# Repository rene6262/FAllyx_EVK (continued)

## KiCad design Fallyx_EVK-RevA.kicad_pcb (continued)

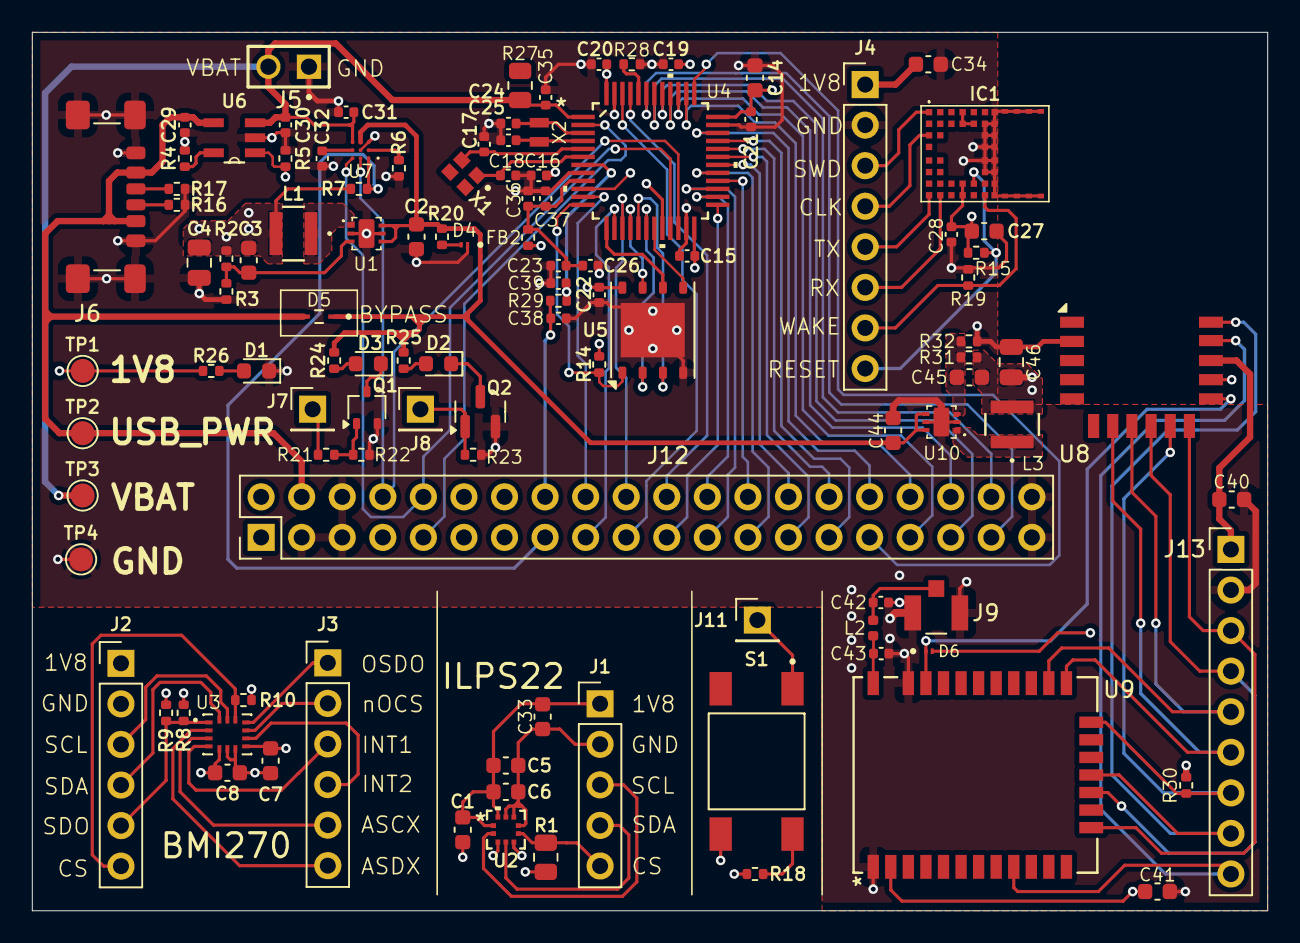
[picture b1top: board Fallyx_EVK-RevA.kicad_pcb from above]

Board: 4 copper layers, 77.3 x 55.0 mm, 112 parts (0 on the bottom side), 95 nets.

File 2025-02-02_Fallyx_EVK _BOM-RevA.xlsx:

Fallyx_EVK BOM |  | RevA
Estimated Cost | 35.42048
Designator | Mfg | Mfg Part ID | Description | QTY | COST/100 | Value | Footprint | ALT P/N
C1, C5, C7, C8, C15, C16, C19, C20, C21, C22, C26, C28, C36 | YAGEO | CC0603KRX7R7BB104 | CAP CER 0.1UF 16V X7R 0603 | 13.0 | 0.0174 | 0.1uF | C0603
C2, C6, C14, C27, C41 | Samsung Electro-Mechanics | CL10A475KP8NNNC | CAP CER 4.7UF 10V X5R 0603 | 5.0 | 0.0171 | 4.7uF | C0603
C3 | KEMET | C0603C151J5GACTU | CAP CER 150PF 50V C0G/NP0 0603 | 1.0 | 0.0164 | 150pF | C0603
C4 | Murata Electronics | GRM21BR61C106KE15K | CAP CER 10UF 16V X5R 0805 | 1.0 | 0.0467 | 10uF | C0805
C23, C31, C35, C37 | Taiyo Yuden | JMK105BJ105KV-F | CAP CER 1UF 6.3V X5R 0402 | 4.0 | 0.0144 | 1uF | C0402
C29, C30 | Murata Electronics | GRM155R60J106ME05D | CAP CER 10UF 6.3V X5R 0402 | 2.0 | 0.0235 | 10uF | C0402
C33 | Samsung Electro-Mechanics | CL10A225KO8NNNC | CAP CER 2.2UF 16V X5R 0603 | 1.0 | 0.0234 | 2.2uF | C0603
C38 | Murata Electronics | GCM155R71H223KA55D | CAP CER 0.022UF 50V X7R 0402 | 1.0 | 0.0128 | 22nF | C0402
C17, C18, C24, C25, C39 | Murata Electronics | GRM1555C1H100JA01D | CAP CER 10PF 50V C0G/NP0 0402 | 5.0 | 0.0116 | 10pF | C0402
C32 | Murata Electronics | GRM155R61A474KE15D | CAP CER 0.47UF 10V X5R 0402 | 1.0 | 0.0364 | 0.47uF | C0402
C34, C40 | Samsung Electro-Mechanics | CL10A226MP8NUNE | CAP CER 22UF 10V X5R 0603 | 2.0 | 0.0714 | 22uF | C0603
D1 | Würth Elektronik | 150060VS75000 | LED GREEN CLEAR 0603 SMD | 1.0 | 0.1098 |  | C0603
D2 | Würth Elektronik | 150060SS75000 | LED RED CLEAR 0603 SMD | 1.0 | 0.1098 |  | C0603
D3 | Würth Elektronik | 150060AS75000 | LED AMBER CLEAR 0603 SMD | 1.0 | 0.1098 |  | C0603
D4 | Kingbright | APG0603SURC-TT | LED RED CLEAR 2SMD | 1.0 | 0.1937 |  | C0201
D5 | onsemi | RB521S30T1G | DIODE SCHOTTKY 30V 200MA SOD523 | DNP | 0.044 |  | SOD523
FB2 | Würth Elektronik | 7427927261 | FERRITE BEAD 600 OHM 0402 4LN | 1.0 | 0.1485
J1 |  |  | 5PIN | DNP
J2, J3 |  |  | 6PIN | DNP
J4 |  |  | 8PIN | DNP
J5 |  |  | DNP | DNP
J6 | GCT | GCT_USB4135-GF-A | USB C REC GF RA 6P SMT & SMT SHE | 1.0 | 0.4418
J12 |  |  | 40PIN | DNP
J13 |  |  | 9PIN | DNP
L1 | Taiyo Yuden | NR3015T4R7M | FIXED IND 4.7UH 1.04A 144MOHM SM | 1.0 | 0.1881 | 4.7uH
R1 | Panasonic Electronic Components | ERJ-6GEY0R00V | RES SMD 0 OHM JUMPER 1/8W 0805 | 1.0 | 0.0208 | 0Ohm | R0805
R2 | TE Connectivity Passive Product | CPF0402B200KE | RES SMD 200K OHM 0.1% 1/16W 0402 | 1.0 | 0.1621 | 200kOhm | R0402
R3 | TE Connectivity Passive Product | CPF0402B150KE1 | RES SMD 150K OHM 0.1% 1/16W 0402 | 1.0 | 0.205 | 150kOhm | R0402
R16, R17 | Panasonic Electronic Components | ERA-2AEB512X | RES SMD 5.1K OHM 0.1% 1/16W 0402 | 2.0 | 0.0911 | 5.1k | R0402
R8, | YAGEO | RC0402JR-07100KL | RES 100K OHM 5% 1/16W 0402 | DNP | 0.0041 | 100k | R0402
R9, R10 | YAGEO | RC0402JR-07100KL | RES 100K OHM 5% 1/16W 0402 | 2.0 | 0.0041 | 100k | R0402
R19 | YAGEO | RC0402JR-07100KL | RES 100K OHM 5% 1/16W 0402 | DNP | 0.0041 | 100k | R0402
R4, R5, R6, R7, R18, R14, R15, R28 | YAGEO | RC0402JR-0710KL | RC0402JR-0710KL | 8.0 | 0.0061 | 10k | R0402
R20, R23, R24, R25, R26, R29 | YAGEO | RC0402JR-071KL | RES 1K OHM 5% 1/16W 0402 | 6.0 | 0.0061 | 1k | R0402
S1 | Same Sky (Formerly CUI Devices) | TS04-66-50-BK-100-SMT | SWITCH TACTILE SPST-NO 0.05A 12V | 1.0 | 0.1441
Q1 | Infineon Technologies | IRLML6344TRPBF | MOSFET N-CH 30V 5A MICRO3/SOT23 | 1.0 | 0.1843 |  | SOT23
Q2 | LRC | LMBT3904WT1G | 40V 150mW 40@0.1mA,10V 200mA NPN SOT-323-3 Bipolar (BJT) ROHS | 1.0 | 0.0133 |  | SOT323
IC1 | onsemi | NCH-RSL10-101S51-ACG | IC RF TXRX+MCU BLE 51SIP | 1.0 | 11.1653
IC2 | Silicon Labs | BGM111A256V21R | RF TXRX MOD BLUETOOTH CHIP SMD | 1.0 | 8.9264
U1 | Torex Semiconductor Ltd | XC9236F08CER-G | IC REG BUCK ADJ 600MA 6USPC | 1.0 | 1.2908 |  | 6-UFDFN
U2 | STMicroelectronics | ILPS22QSTR | SENSOR 58.89PSIA 24BIT 10HLGA | 1.0 | 2.491 |  | 10-WFLGA
U3 | Bosch Sensortec | BMI270 | IMU ACCEL/GYRO I2C/SPI 14LGA | 1.0 | 3.0347 |  | 14HLGA
U4 | STMicroelectronics | STM32L431CBT6 | IC MCU 32BIT 128KB FLASH 48LQFP | 1.0 | 2.11713 |  | 48-LQFP
U5 | Macronix | MX25R6435FZNIL0 | IC FLASH 64MBIT SPI/QUAD 8WSON | 1.0 | 1.54675
U6 | Microchip Technology | MCP73831T-2ACI/OT | IC BATT CNTL LI-ION 1CEL SOT23-5 | 1.0 | 0.6125 |  | SOT235
X1 | ECS Inc. | ECS-320-CDX-2094 | CRYSTAL 32.000MHZ 10PF SMD | 1.0 | 0.3976
X2 | Jauch Quartz | Q 0,032768-JTX110-9-20-T1-90K-LF | CRYSTAL 32.7680KHZ 9PF SMD | 1.0 | 0.7786

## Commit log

2025-01-29 continued design work
2025-01-30 review edits
2025-02-08 Updated for new BLE modules
2025-02-17 Final Routing and export for EVK
2025-07-01 final commit
